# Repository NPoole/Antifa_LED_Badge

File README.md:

# Antifa_LED_Badge
Simple backlit PCB pin and illuminated reminder to oppose fascism in all forms ✊

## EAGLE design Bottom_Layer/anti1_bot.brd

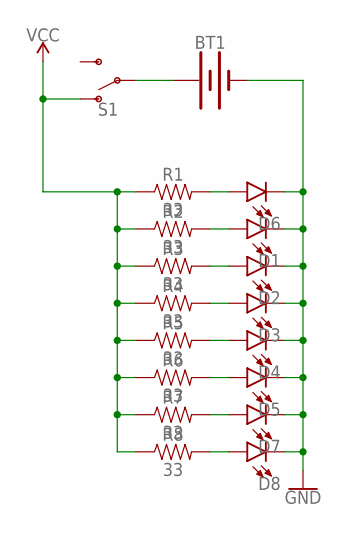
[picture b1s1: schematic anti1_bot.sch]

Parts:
BT1: BATTERY-20MM_SMD_4LEGS; BATTCON_20MM_4LEGS
D1, D2, D3, D4, D5, D6, D7, D8: LED0603; LED-0603
R1, R2, R3, R4, R5, R6, R7, R8: 33; 0603
S1: SWITCH-SPDT-SMD-AYZ0202; SWITCH_DPDT_SMD_AYZ0202

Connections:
GND: BT1.NEGATIVE (-), D1.C, D2.C, D3.C, D4.C, D5.C, D6.C, D7.C, D8.C
unnamed: BT1.POSITIVE@1 (+), BT1.POSITIVE@2 (+), BT1.POSITIVE@3 (+), BT1.POSITIVE@4 (+), S1.2
unnamed: D4.A, R5.2
unnamed: D6.A, R1.2
unnamed: D1.A, R2.2
unnamed: D2.A, R3.2
unnamed: D3.A, R4.2
unnamed: D5.A, R6.2
unnamed: D7.A, R7.2
unnamed: D8.A, R8.2
VCC: R1.1, R2.1, R3.1, R4.1, R5.1, R6.1, R7.1, R8.1, S1.1 (O)

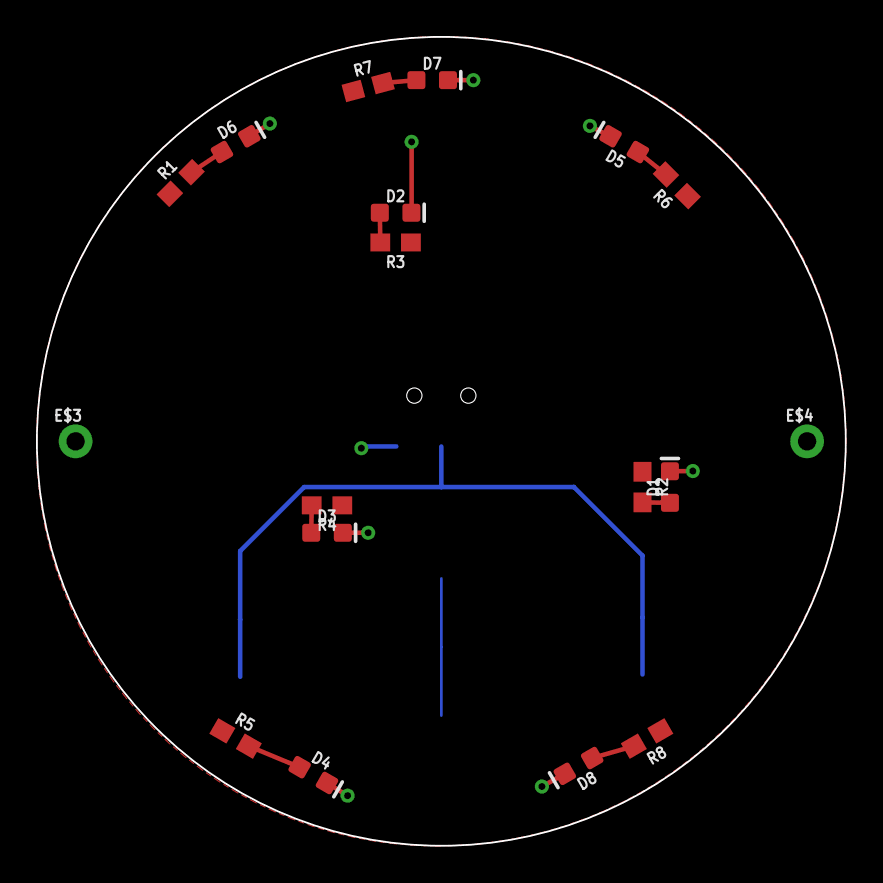
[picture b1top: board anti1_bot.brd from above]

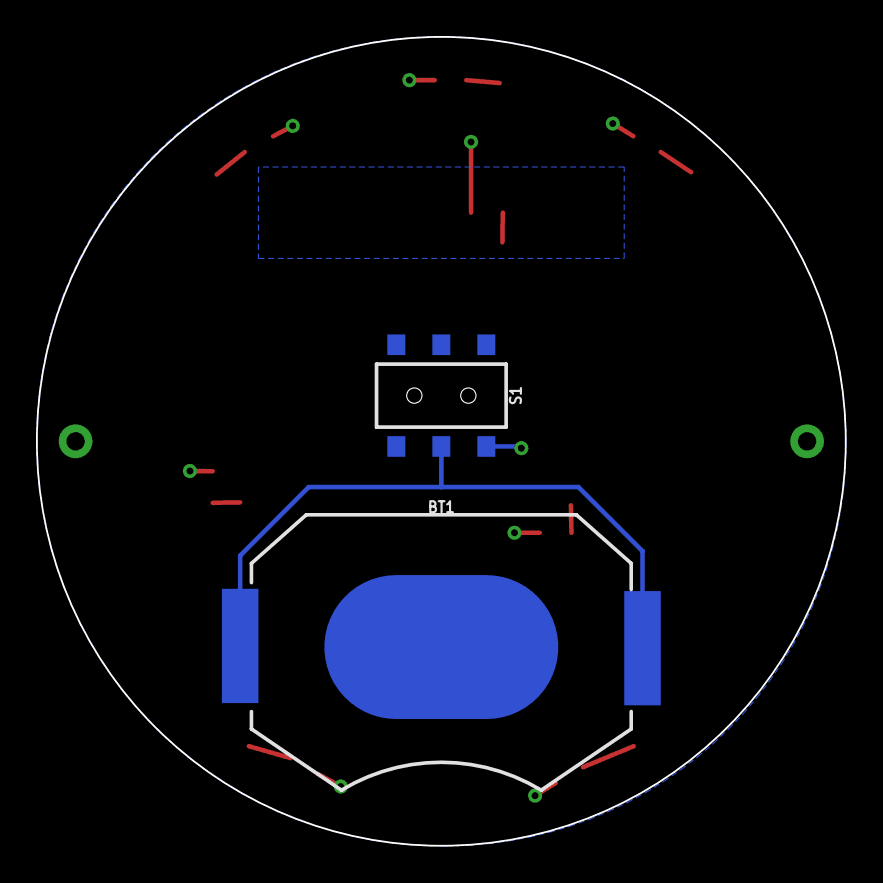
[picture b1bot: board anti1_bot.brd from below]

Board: 2 copper layers, 44.9 x 44.9 mm, 20 parts (2 on the bottom side), 11 nets.

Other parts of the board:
E$3, E$4: 1X01_NO_SILK

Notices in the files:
parts and their libraries:
SparkFun-Connectors: Licensing: Creative Commons ShareAlike 4.0 International - https://creativecommons.org/licenses/by-sa/4.0
